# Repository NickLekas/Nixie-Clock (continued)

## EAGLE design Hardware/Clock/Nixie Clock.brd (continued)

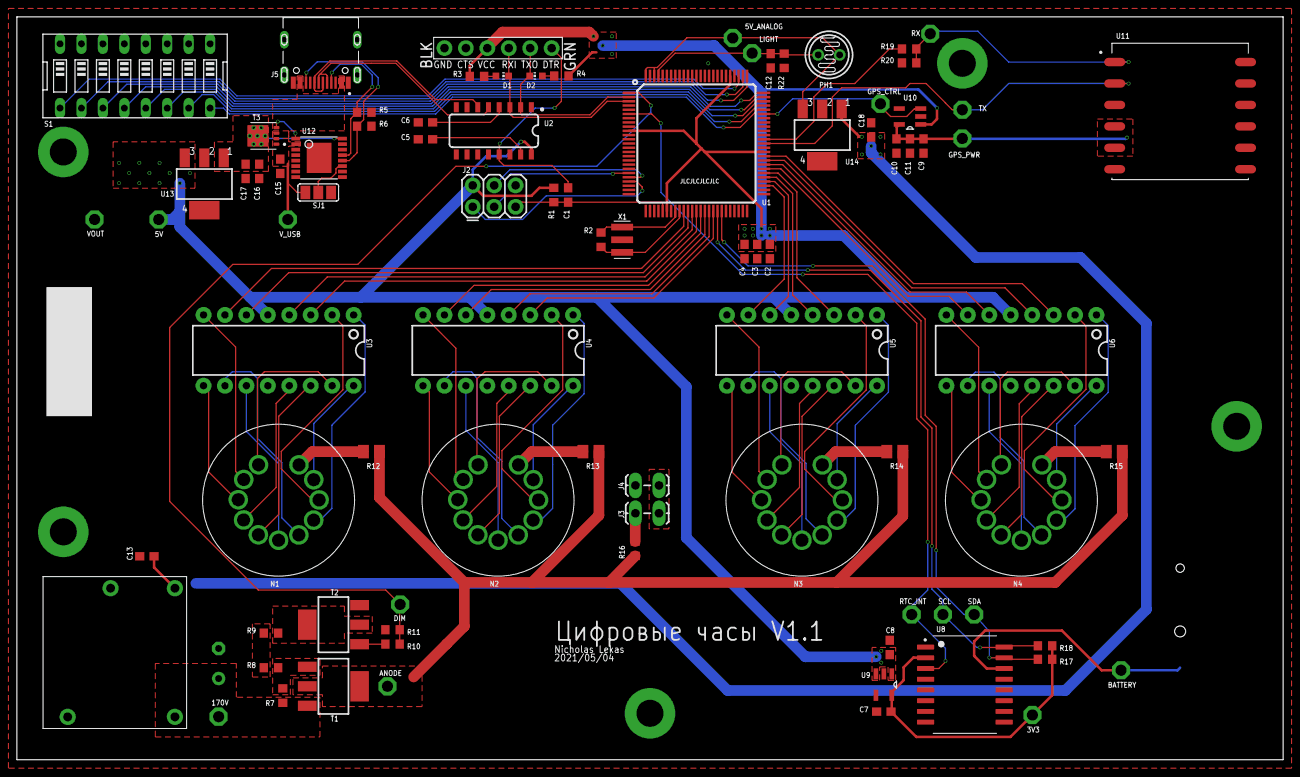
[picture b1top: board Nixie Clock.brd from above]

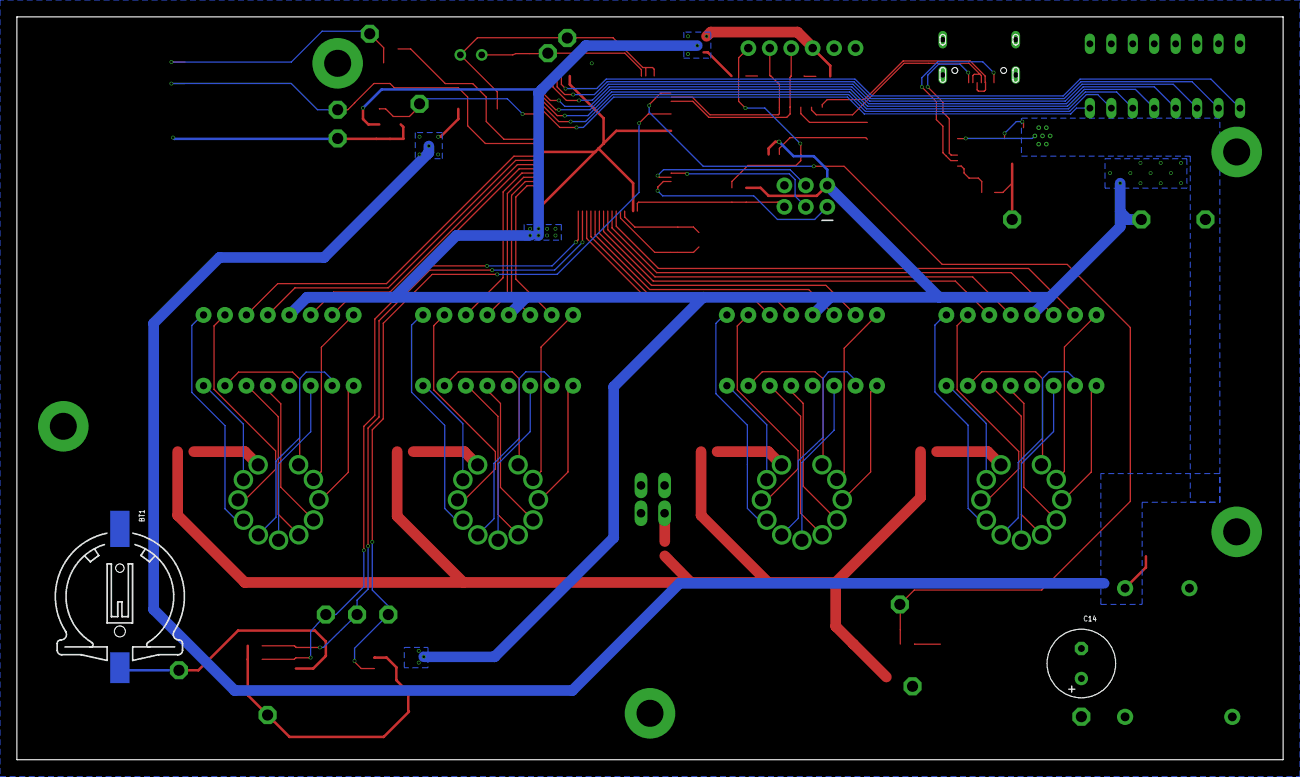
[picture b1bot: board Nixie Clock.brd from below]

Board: 2 copper layers, 150.0 x 88.0 mm, 89 parts (2 on the bottom side), 112 nets.

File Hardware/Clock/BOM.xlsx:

v1.0
Ref des | Quantity | value | Component | Package
C1, C2, C3, C4, C6, C10, C11 | 7 | 0.1uF |  | 0603 | 1
C17, C18 | 2 | 0.22uF |  | 0603 | 1
C13 | 1 | 100uF |  | 0603
C5, C9, C12, C16 | 4 | 10uF |  | 0603 | 1
C7, C8, C15 | 3 | 1uF |  | 0603 | 1
C14 | 1 | 4.7uf | 200V + | E3,5-8 | 1
R7, R8, R9, R16 | 4 | 100k | 1/3 W | 0603 | 1
R1, R3, R4, R5, R6, R10, R11, R17, R18, R19, R20, R21, R22 | 13 | 10k |  | 0603 | 1
R12, R13, R14, R15 | 4 | 10k | 1/2 W | 0805 | 1
R2 | 1 | 1M |  | 0603 | 1
D1, D2 | 2 | Green |  | 0603 | 1
U3, U4, U5, U6 | 4 |  | K155ID1 | DIP 16 | 1
U1 | 1 |  | ATmega2560-16AU | TQFP100 | 1
U2 | 1 |  | CH340C | SOP-16 |  | lcsc | https://lcsc.com/product-detail/USB-ICs_WCH-Jiangsu-Qin-Heng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
U8 | 1 |  | DS3231SN#T&R | SOIC-16 | 1
U12 | 1 |  | IP2721 | TSSOP-16 | 1 | lcsc | https://lcsc.com/product-detail/Interface-Specialized_INJOIN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
U11 | 1 |  | L80-M39 | LCC | 1 | lcsc | https://lcsc.com/product-detail/Satellite-Positioning-Module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
U13, U14 | 2 |  | LM340MP-5.0/NOPB | SOT-223 | 1
U9, U10 | 2 |  | MIC5205-3.3YM5-TR | SOT-23-5 |  | lcsc
U7 | 1 |  | NCH8200HV |  | 1
S1 | 1 |  | SW_DIP-8 | DIP-16 | 1
T3 | 1 |  | CSD18543Q3A | VSONP-8 | 1
T1 | 1 |  | PZTA92 | SOT-223 | 1
T2 | 1 |  | PZTA42 | SOT-223 | 1
PH1 | 1 |  | GM5539 |  | 1
BT1 | 1 |  | 1056 or CR1220-2 |  | 1
X1 | 1 |  | CSTNE16M0V53C000R0 |  | 1
J4 | 1 |  | HRO_TYPE-C-31-M-12 |  |  | lcsc | https://lcsc.com/product-detail/USB-Connectors_Hanbo-Electro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
N1, N2, N3, N4 | 4 |  | ИН-8 |  | 1
v1.1
Ref des | Quantity | value | Component | Package
C1, C2, C3, C4, C6, C10, C11 | 7 | 0.1uF |  | 0603
C17, C18 | 2 | 0.22uF |  | 0603
C13 | 1 | 100uF |  | 0603
C5, C9, C12, C16 | 4 | 10uF |  | 0603
C7, C8, C15 | 3 | 1uF |  | 0603
C14 | 1 | 4.7uf | 200V + | E3,5-8
R7, R8, R9, R16 | 4 | 100k | 1/3 W | 0603
R1, R10, R11, R17, R18, R20, R22 | 7 | 10k |  | 0603
R3, R4, R5, R6, R19 | 5 | 5.1k |  | 0603
R12, R13, R14, R15 | 4 | 10k | 1/2 W | 0805
R2 | 1 | 1M |  | 0603
D1, D2 | 2 | Green |  | 0603
U3, U4, U5, U6 | 4 |  | K155ID1 | DIP 16
U1 | 1 |  | ATmega2560-16AU | TQFP100
U2 | 1 |  | CH340C | SOP-16 | lcsc | https://lcsc.com/product-detail/USB-ICs_WCH-Jiangsu-Qin-Heng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
U8 | 1 |  | DS3231SN#T&R | SOIC-16
U12 | 1 |  | IP2721 | TSSOP-16 | lcsc | https://lcsc.com/product-detail/Interface-Specialized_INJOIN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
U11 | 1 |  | L80-M39 | LCC | lcsc | https://lcsc.com/product-detail/Satellite-Positioning-Module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
U13, U14 | 2 |  | LM340MP-5.0/NOPB | SOT-223
U9, U10 | 2 |  | MIC5205-3.3YM5-TR | SOT-23-5 | lcsc
U7 | 1 |  | NCH8200HV
S1 | 1 |  | SW_DIP-8 | DIP-16
T3 | 1 |  | CSD18543Q3A | VSONP-8
T1 | 1 |  | PZTA92 | SOT-223
T2 | 1 |  | PZTA42 | SOT-223
PH1 | 1 |  | GM5539
BT1 | 1 |  | 1056 or CR1220-2
X1 | 1 |  | CSTNE16M0V53C000R0
J4 | 1 |  | 12402012E212A
N1, N2, N3, N4 | 4 |  | ИН-8

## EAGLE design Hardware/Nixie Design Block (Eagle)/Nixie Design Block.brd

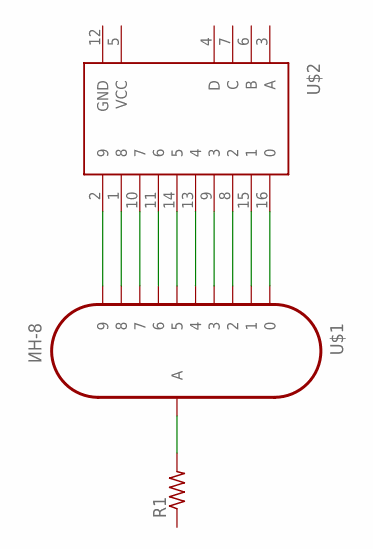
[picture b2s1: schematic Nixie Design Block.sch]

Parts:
R1: R-US_M0805; M0805
U$1: ИН-8; IN-8_SOCKET
U$2: K155ID1; DIL16-KIT

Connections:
unnamed: U$1.9, U$2.2 (9)
unnamed: U$1.8, U$2.1 (8)
unnamed: U$1.7, U$2.10 (7)
unnamed: U$1.6, U$2.11 (6)
unnamed: U$1.5, U$2.14 (5)
unnamed: U$1.4, U$2.13 (4)
unnamed: U$1.3, U$2.9 (3)
unnamed: U$1.2, U$2.8 (2)
unnamed: U$1.1, U$2.15 (1)
unnamed: U$1.0, U$2.16 (0)
unnamed: R1.2, U$1.A

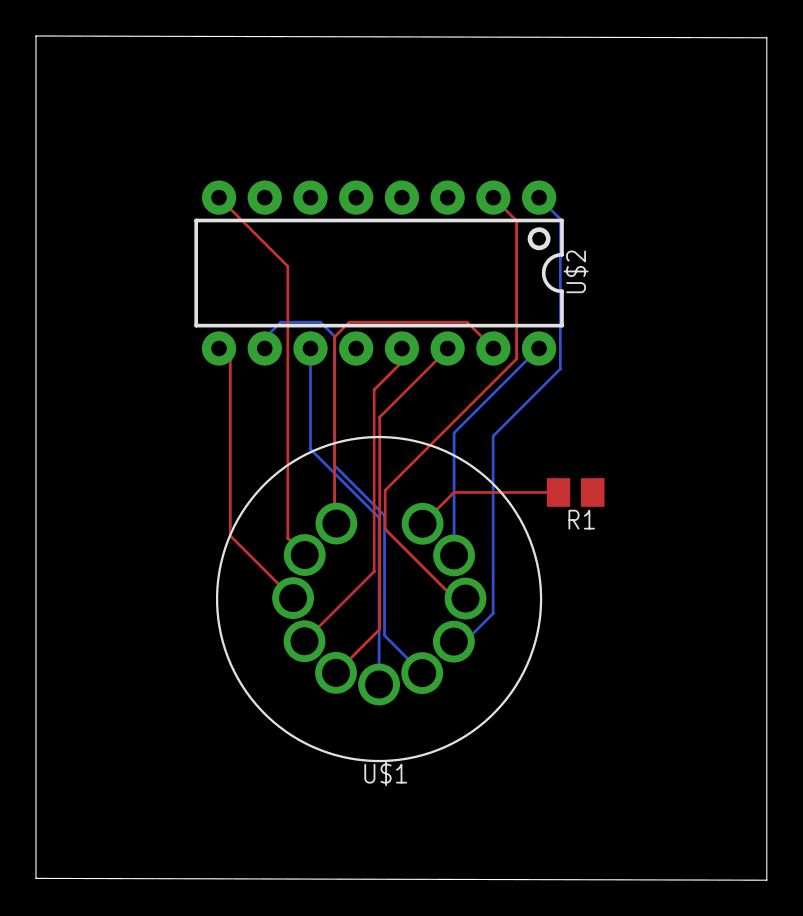
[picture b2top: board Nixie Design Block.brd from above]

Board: 2 copper layers, 40.6 x 46.9 mm, 3 parts (0 on the bottom side), 11 nets.

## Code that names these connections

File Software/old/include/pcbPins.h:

#ifndef PCBPINS_H
#define PCBPINS_H

//GPS pins
#define gpsSerial Serial3 //RX:PJ0 TX:PJ1
const int gpsCtrl = 39; //PG2

//dimming pins
const int dim = 5; //PG5
const int light = 54; //A0 PF0

//dip switch pins
//time set pins
const int dst = 29; //1 PA7
const int timeMode = 28; //2 PA6
const int plusMinus = 27; //3 PA5
const int eight = 26; //4 PA4
const int four = 25; //5 PA3
const int two = 24; //6 PA2
const int one = 23; //7 PA1
//extra pin allotted for latter potential expansion
const int extra1 = 22; //8 PA0

//digit pins
//minutes ones
const int minOnesA = 30; //PC7
const int minOnesB = 32; //PC5
const int minOnesC = 33; //PC4
const int minOnesD = 31; //PC6

//minutes tens
const int minTensA = 34; //PC3
const int minTensB = 36; //PC1
const int minTensC = 37; //PC0
const int minTensD = 35; //PC2

//hours ones
const int hrOnesA = 42; //PL7
const int hrOnesB = 44; //PL5
const int hrOnesC = 45; //PL4
const int hrOnesD = 43; //PL6

//hours tens
const int hrTensA = 46; //PL3
const int hrTensB = 48; //PL1
const int hrTensC = 49; //PL0
const int hrTensD = 47; //PL2

//RTC
const int rtcInt = 2; //PE4

#endif

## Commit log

2019-09-13 Removed build_flags from platfromio.ini
2019-09-13 REmoved build_flages from platformio.ini
2019-09-13 Added basic RTC functionality
2019-09-13 added comments to code
2019-09-13 Added Serial debug messages
2019-09-13 added settings.json to gitignore
2019-09-14 added link to new RTC library
2019-09-14 Added daily RTC time update using GPS
2019-09-14 Changed GPS pins and added GPS power control pin
2019-09-14 Tweakedtime update function
2019-09-14 Changed variable names
2019-09-14 Fixed syntax error
2019-09-14 Disabled nightly time update
2019-09-14 Removed manufaturing files from the PCF8574 library
2019-09-15 Seperated nixie control, gps, and rtc functions into their own files
2019-09-15 Added missing header file to gps.h
2019-09-15 Added GPS power control functions
2019-09-15 Implemented turning the GPS on and off when updating the time
2019-09-18 improved code efficency
2019-09-24 fixed formatting
2019-11-06 Added daylight savings toggle and moved confg file
2019-12-18 changed pin definitions from defines to const ints and added dip switch time zone functionality
2019-12-18 moved the timezone set code from getRTCTime() to setRTCtime to improve efficiency
2019-12-18 changed 12 hour mode secection to a dip switch
2019-12-18 changes the nixie pinmode setup for loop form a hard coded range to the variable numbers
2019-12-18 changed dip switch pins
2019-12-19 added ProMini to platform.ini
2020-01-27 changed to arduino mega, re-assigned pins, adjusted functions to work without IO expanders
2020-01-27 removed all IO expander coder and added propper RTC initiation
2020-02-02 removed all reference to the IO expander and atmega328p controllers
2020-02-02 removed IO expander library call in nixie.h
2020-02-02 added library comments
2020-03-25 removed main.h
2020-03-25 moved header files to the include folder
2020-03-25 changed config to debug
2020-03-25 added light based nixie dimming
2020-03-25 removed delay every 60 seconds for time checking and implemented light based dimming
2020-03-26 added switch labels
2020-03-26 added pcb pins file and a toggle to switch between pins files in debug
2020-03-26 added pcb pins and ic labels
2020-03-26 added rtc interupt pin
2020-03-26 rearranged pcb pins
2020-03-27 moved switch reading from setRTCTime() to dedicated function that runs in getRTCTime()
2020-03-27 moved the time bound check from readSettings() to getRTCTime()
2020-03-28 added a call to dimming durring setup()
2020-03-28 modified dimming() to work with the LDR
2020-03-31 Added PWM minimum bounding and a pull to full brightness when close to max
2020-04-03 Added new PWM functions to lower frequency
2020-04-06 changed dimming pin to work with the PWM frequency library
2020-04-06 rearranged setting switch functions
2020-04-08 Added a dimming function that uses a pot for PWM tuning and lowered the min PWM value for 60Hz
2020-04-15 lowered voltage to trigger max brightness
2020-04-15 added rtc power loss recovery
2020-04-15 set tube brightness to max durrring setup
2020-04-15 removed powerloss check invert to work corectly
2020-04-15 fixed initial pwm write argument order
2020-04-15 removed duplicate call to GPSInit()
2020-04-15 added fade down to brighntess after startup
2020-04-18 refreshed libraries
2020-04-18 added averaging to the light value
2020-12-26 updated libraries
2020-12-26 removed the need for software serial from the GPS library
2020-12-27 Removed averaging code that was causing the PWM signal to be unstable
2020-12-29 Found the ideal PWM frequency and added a 4.7uF capacitor to the output of the nixie supply to eliminate audible coil whine
2020-12-30 Modified to use the new npn dimming circuit
2020-12-30 Improved comments
2020-12-30 Changed the display update to only update the display if the time has changed
2020-12-31 Fixed minor formmating issues
2021-01-04 Adjusted the maxPWM value for the new current limiting resistors
2021-01-04 Added more control over debug options
2021-01-04 Initial commit of the power control code
2021-01-04 Changed programPD() to be hardcoded for 9V 2A (18W) instead of user controllable
2021-01-04 fixed order of operation error and found that wrire() was missing at the end of programPD()
2021-05-21 Change pin assignments to match the PCB
2021-05-26 Create Software
2021-05-26 Delete Software
    Accidentally added
2021-05-26 Create test
2021-05-26 Moved all code to the Softwalre folder
2021-05-26 Started tracking the Software folder
2021-05-26 Added PCB files to Hardware
2021-05-29 Added a toggle to set the RTS using current time when uploading code
2021-05-29 Changed the PWM pin from 4 to 5
2021-05-29 Added 1 second delay when polling the GPS for new data
2021-05-29 Changed the settings pins initilization order to match the PCB pin order
2021-05-29 Seperated minute and hour pin initilazation to match the PCB pin order and disabled PWM frequency control. PWM frequency control will be added back latter
2021-05-29 Added the ability to set RTC time when uploading code and switched from signed binary to multiply by -1 for setting the time zone
2021-05-29 Stoped tracking the eagle project file and added a gitignorefile
2021-05-29 Set PWM to 120Hz using register control
2021-06-01 rearranged the hardware file structure and added the KiCad files
2021-06-01 Moved all KiCad files into a dedicated folder
2021-06-01 added comments about KiCad version used and what v1.05 is
2021-06-02 Added a minimum PWM value to keep the tubes from turning off or partially igniting in the dark
2021-09-22 Create README.md
    initial readme commit
2021-09-22 Create LICENSE
2021-10-10 Update LICENSE
2022-07-21 Redoing code to be more efficent
2022-07-21 worked on initial file setup, completed initial nixie.cpp
2022-07-21 completed settings.h initial code
2023-09-29 Added folders for v2 and started hardware design
2023-10-14 added schematic pages and HV switching circuit
2023-10-22 Complteted schematic, mergerd schematic on to one sheet, started assigning footprints
2023-10-22 removed empty schematic sheets left from the 1 page merge
2023-10-23 Finished assigning footprints and started layout
2023-10-23 Continued work on layout
2024-08-23 replaced old nixie compontes with new library and replaced IO expander with QFN
2024-08-24 Creating seperate processing and nixie boards for furture modularity
2024-08-25 seperated the processor and nixie boards
2024-08-27 Assigned footprints
2024-09-01 Started board layout
2024-09-02 Laied out indivdual circuit blocks
2024-09-02 Started placing assembled blocks on the board and routing
2024-09-02 started nixie layout, added bleed resistor to HV cap
2024-09-02 Completed initial layout of the IN-8 board
2024-09-03 finished initial layout and swapped SDA/SCL on connector
2025-02-03 added ground via stitching, and baord names, version, designer, and date to silkscreen
